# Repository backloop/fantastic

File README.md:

# fantastic

ATmega-based inline fan tachometer frequency multiplier for low-RPM PWM fans on motherboards that expect higher tachometer rates.

## Problem Background

The target motherboard (Supermicro X10SLM-F) fan controller is designed for high-speed fans and tends to report low-RPM Noctua fans as `0 RPM` intermittently, especially below ~300 RPM.

When this happens, the board reacts aggressively:
- temporary non-recoverable (`nr`) fan status,
- fan fail warnings,
- fan duty jumping to 100% until tachometer readings recover.

Even after lowering thresholds through IPMI, false `0 RPM` detections may still happen.

## Solution

Use a small ATmega board inline on the tachometer path:
- read incoming fan tachometer pulses,
- calculate frequency/RPM,
- generate a new tachometer output waveform multiplied by `x4`,
- feed that multiplied signal to the motherboard fan header.

With a `x4` multiplier, a real fan range of roughly `150-1500 RPM` appears as `600-6000 RPM` to the motherboard.

## Repository Contents

- `fantastic.ino`: firmware for measurement, filtering, and output waveform generation.

## Hardware Design Files

> Warning: The documented KiCad schematic/PCB has not been validated in a physical PCB build yet. Current results are from the initial hand-built proto-board prototype.

- Schematic PDF: [`media/schematics.pdf`](media/schematics.pdf)

Schematic preview (page 1):

3D board view:

## Firmware Behavior

The sketch:
- reads tach pulses using interrupt-based timing (`PIN_SENSE = 2`),
- smooths period jitter using a short rolling average,
- computes input RPM/frequency,
- updates output only when the measured input frequency changes,
- generates output tach waveform on `PIN_TACH_OUT = 9` (Timer1, 50% duty),
- optionally generates 25 kHz fan-control PWM on `PIN_PWM_OUT = 3` (Timer2).

Default behavior keeps interrupt-based measurement enabled and serial command input configured for PWM duty testing.

## IPMI Threshold Examples

### Baseline (often insufficient for low-RPM fans)

```bash
ipmitool sensor thresh "FAN2" lower 0 0 100
```

### Thresholds used with x4 multiplier

```bash
ipmitool sensor thresh "FAN2" lower 300 400 500
ipmitool sensor thresh "FAN2" upper 6500 6600 6700
```

### Live monitoring

```bash
while true; do ipmitool sensor | grep "FAN[2,4]"; sleep 1; done
```

## Example Runtime Output

```text
Input :                 Freq (mHz): 9174        Freq (Hz): 9    RPM: 275
Output:                 Freq (mHz): 36696       Freq (Hz): 37   RPM: 1100
```

The output updates only when input frequency changes, reducing unnecessary reprogramming of timer TOP values.

## Sample Sensor Output Reference

### Before multiplier (example with intermittent low/zero readings)

| Sensor | Reading | Unit | Status | LNR | LCR | LNC | UNC | UCR | UNR |
|---|---:|---|---|---:|---:|---:|---:|---:|---:|
| FAN2 | 300.000 | RPM | ok | 0.000 | 0.000 | 100.000 | 1700.000 | 1800.000 | 1900.000 |
| FAN4 | 200.000 | RPM | ok | 0.000 | 0.000 | 100.000 | 1700.000 | 1800.000 | 1900.000 |
| FAN2 | 300.000 | RPM | ok | 0.000 | 0.000 | 100.000 | 1700.000 | 1800.000 | 1900.000 |
| FAN4 | 0.000 | RPM | nr | 0.000 | 0.000 | 100.000 | 1700.000 | 1800.000 | 1900.000 |
| FAN2 | 1400.000 | RPM | ok | 0.000 | 0.000 | 100.000 | 1700.000 | 1800.000 | 1900.000 |
| FAN4 | 1200.000 | RPM | ok | 0.000 | 0.000 | 100.000 | 1700.000 | 1800.000 | 1900.000 |
| FAN2 | 300.000 | RPM | ok | 0.000 | 0.000 | 100.000 | 1700.000 | 1800.000 | 1900.000 |
| FAN4 | 300.000 | RPM | ok | 0.000 | 0.000 | 100.000 | 1700.000 | 1800.000 | 1900.000 |

### After multiplier + adjusted thresholds

| Sensor | Reading | Unit | Status | LNR | LCR | LNC | UNC | UCR | UNR |
|---|---:|---|---|---:|---:|---:|---:|---:|---:|
| FAN2 | 800.000 | RPM | ok | 300.000 | 400.000 | 500.000 | 6500.000 | 6600.000 | 6700.000 |
| FAN4 | 1100.000 | RPM | ok | 300.000 | 400.000 | 500.000 | 6500.000 | 6600.000 | 6700.000 |

Observed steady-state mapping from original fan RPM to reported RPM:

| Channel | Original RPM | Multiplied RPM |
|---|---:|---:|
| FAN2 | 200 | 800 |
| FAN4 | 275 | 1100 |

## Sample Serial Log Reference

```text
Input :                 Freq (mHz): 9174        Freq (Hz): 9    RPM: 275
Output:                 Freq (mHz): 36696       Freq (Hz): 37   RPM: 1100

Input :                 Freq (mHz): 9174        Freq (Hz): 9    RPM: 275
Input :                 Freq (mHz): 9174        Freq (Hz): 9    RPM: 275
Input :                 Freq (mHz): 9174        Freq (Hz): 9    RPM: 275
Input :                 Freq (mHz): 9091        Freq (Hz): 9    RPM: 273
Output:                 Freq (mHz): 36364       Freq (Hz): 36   RPM: 1092

Input :                 Freq (mHz): 9091        Freq (Hz): 9    RPM: 273
Input :                 Freq (mHz): 9174        Freq (Hz): 9    RPM: 275
Output:                 Freq (mHz): 36696       Freq (Hz): 37   RPM: 1100
```

## Design Goals

Input range:
- RPM: `0-2000`
- Frequency: `0-33 Hz`

Output range (with x4 multiplier):
- RPM: `0-8000`
- Frequency: `0-133 Hz`

## Hardware Notes / Lessons Learned

- Use a common ground between fan supply (12V domain) and ATmega (5V domain).
- 25 kHz PWM noise can couple into tachometer/ground; use RC filtering on tach input.
- Use a base resistor on the open-collector NPN stage to keep logic-high levels well-behaved.
- Verify both input and output waveforms on an oscilloscope during bring-up.

## Fan Reference

Noctua PWM specification white paper:
- https://noctua.at/pub/media/wysiwyg/Noctua_PWM_specifications_white_paper.pdf

Measured Noctua F/P12 duty-to-RPM values:

| PWM duty | RPM |
|---|---:|
| 100% | 1364 |
| 90% | 1200 |
| 80% | 1111 |
| 70% | 1000 |
| 60% | 882 |
| 50% | 750 |
| 40% | 588 |
| 30% | 417 |
| 20% | 291 |
| 10% | 137 |
| 0% | 0 |

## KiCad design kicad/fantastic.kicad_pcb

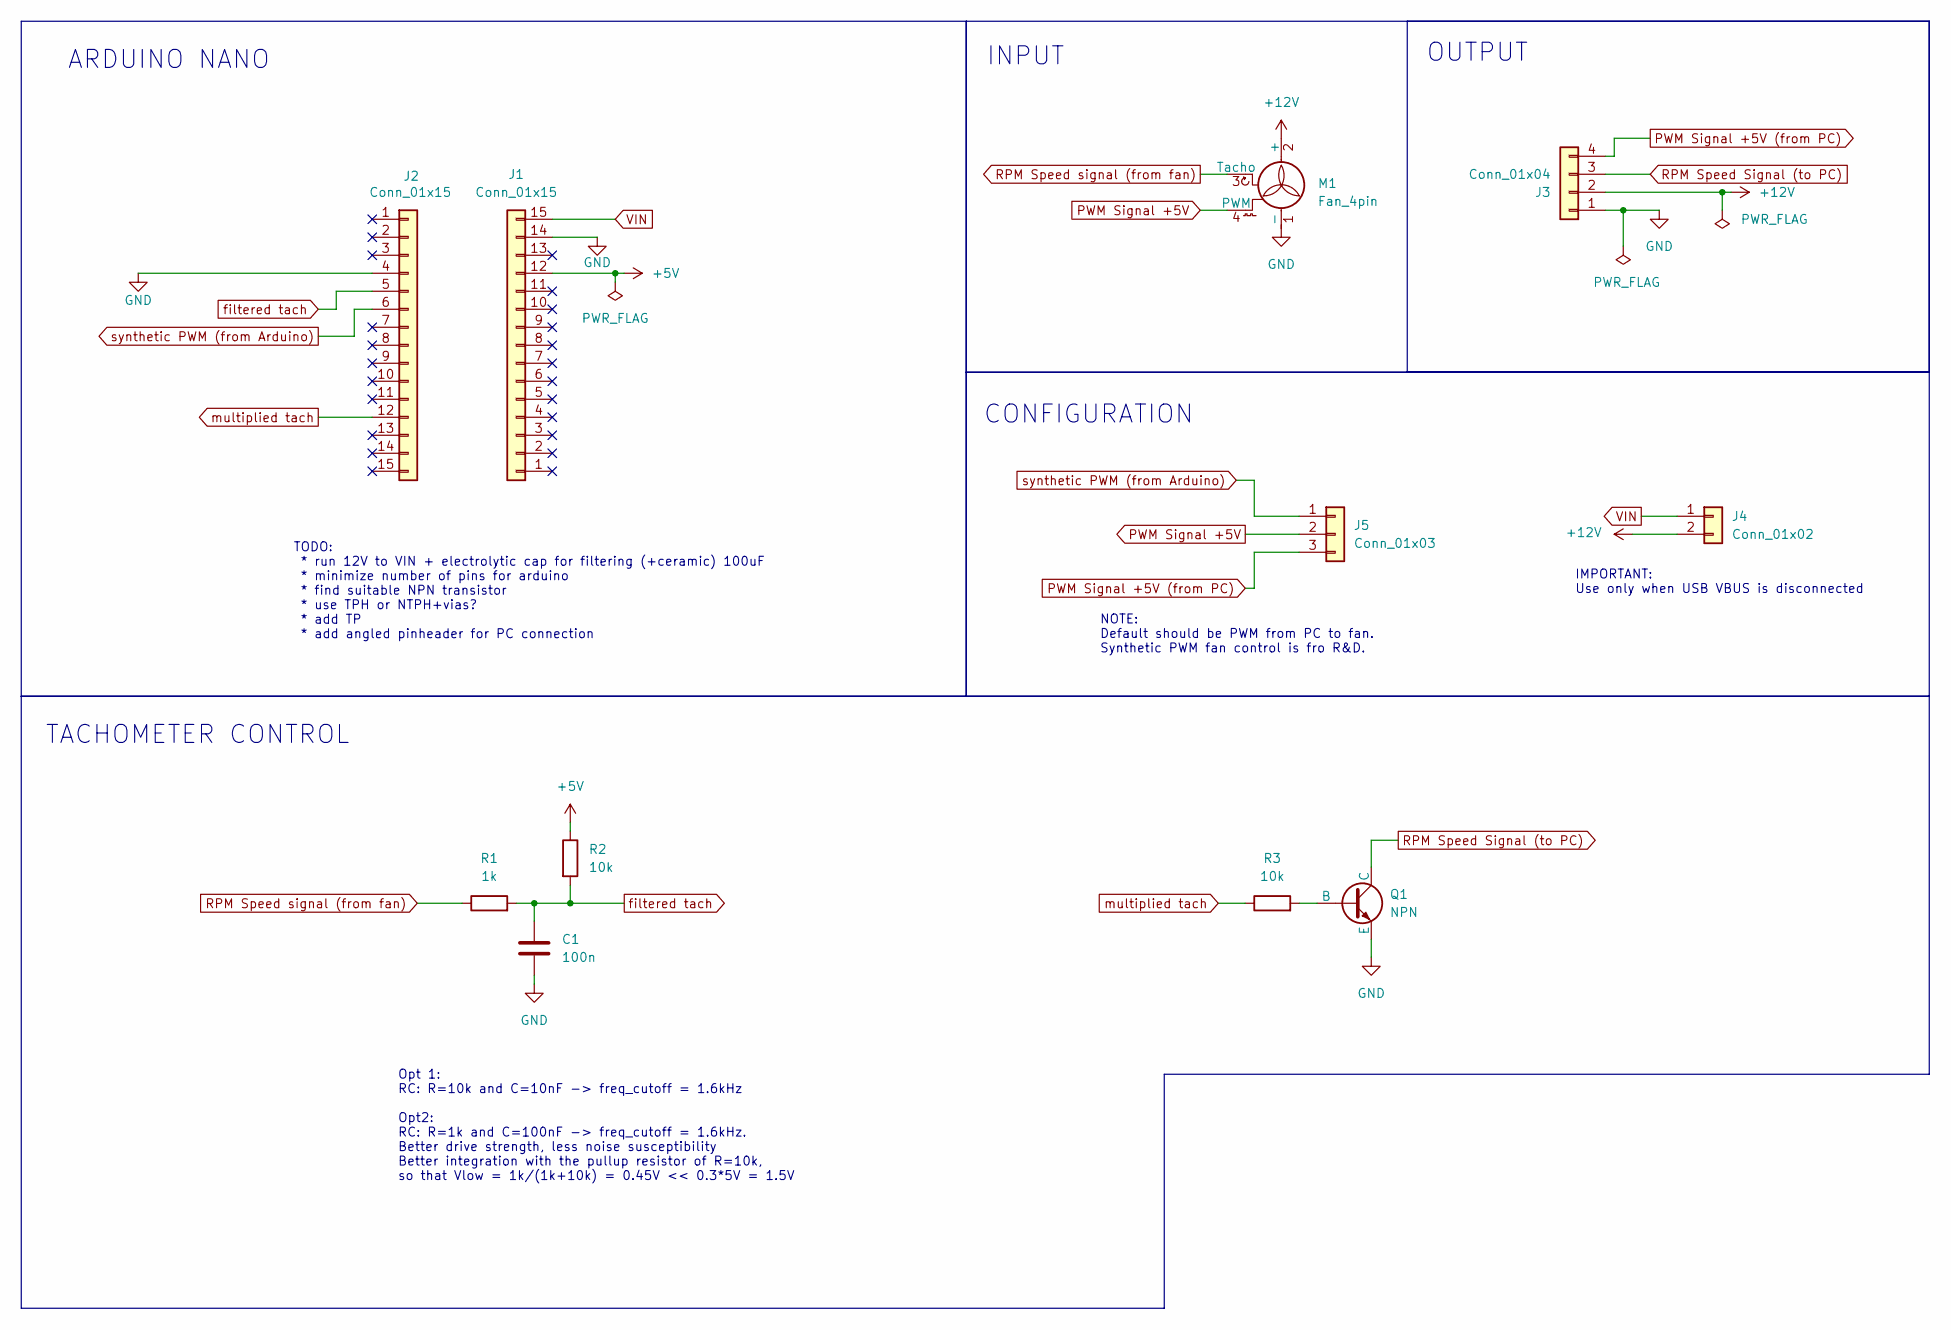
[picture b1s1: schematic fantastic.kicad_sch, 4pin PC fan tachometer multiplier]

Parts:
C1: 100n; C_0603_1608Metric
J1, J2: Conn_01x15; PinHeader_1x15_P2.54mm_Vertical
J3: Conn_01x04; PinHeader_1x04_P2.54mm_Vertical
J4: Conn_01x02; PinHeader_1x02_P2.54mm_Vertical
J5: Conn_01x03; PinHeader_1x03_P2.54mm_Vertical
M1: Fan_4pin; FanPinHeader_1x04_P2.54mm_Vertical
Q1: NPN; SOT-23_Handsoldering
R1: 1k; R_0603_1608Metric
R2, R3: 10k; R_0603_1608Metric

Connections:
+5V: J1.12, R2.1
+12V: J3.2, J4.2, M1.2 (+)
GND: C1.2, J1.14, J2.4, J3.1, M1.1 (-), Q1.3 (E)
unnamed: Q1.2 (B), R3.2
PWM Signal +5V: J5.2, M1.4 (PWM)
PWM Signal +5V (from PC): J3.4, J5.3
RPM Speed Signal (to PC): J3.3, Q1.1 (C)
RPM Speed signal (from fan): M1.3 (Tacho), R1.1
VIN: J1.15, J4.1
filtered tach: C1.1, J2.5, R1.2, R2.2
multiplied tach: J2.12, R3.1
synthetic PWM (from Arduino): J2.6, J5.1

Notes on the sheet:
NOTE: Default should be PWM from PC to fan. Synthetic PWM fan control is fro R&D.
ARDUINO NANO
TACHOMETER CONTROL
Opt 1: RC: R=10k and C=10nF -> freq_cutoff = 1.6kHz Opt2: RC: R=1k and C=100nF -> freq_cutoff = 1.6kHz. Better drive strength, less noise susceptibility Better integration with the pullup resistor of R=10k, so that Vlow = 1k/(1k+10k) = 0.45V << 0.3*5V = 1.5V
OUTPUT
INPUT
IMPORTANT: Use only when USB VBUS is disconnected
CONFIGURATION
TODO: * run 12V to VIN + electrolytic cap for filtering (+ceramic) 100uF * minimize number of pins for arduino * find suitable NPN transistor * use TPH or NTPH+vias? * add TP * add angled pinheader for PC connection

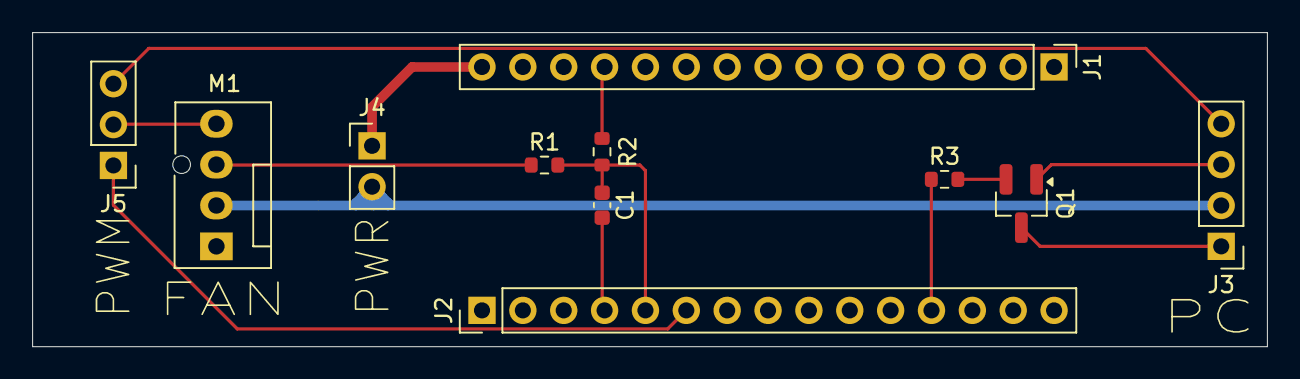
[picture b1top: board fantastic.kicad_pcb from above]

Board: 2 copper layers, 76.8 x 19.5 mm, 11 parts (0 on the bottom side), 12 nets.

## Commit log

2026-03-03 fantastic.ino: Working 4x tachometer frequency multiplication
2026-03-03 README.md: Extract documentation from fantastic.ino
2026-03-03 kicad: Add schematics and layout files
2026-03-03 README.md: Added schematics and layout
2026-03-03 README.md: Add reference to hardware design files
2026-03-03 README.md: Add inline schematics
2026-03-03 README.md: Clarify which hardware has been verified
2026-03-06 .gitignore: Add kicad related exclusions
2026-03-17 README.md: Add fan_control_sketch.svg as visual explanation
